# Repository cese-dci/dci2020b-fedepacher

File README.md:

Repositorio para la materia Diseño de Circuitos Impresos de la CESE2020

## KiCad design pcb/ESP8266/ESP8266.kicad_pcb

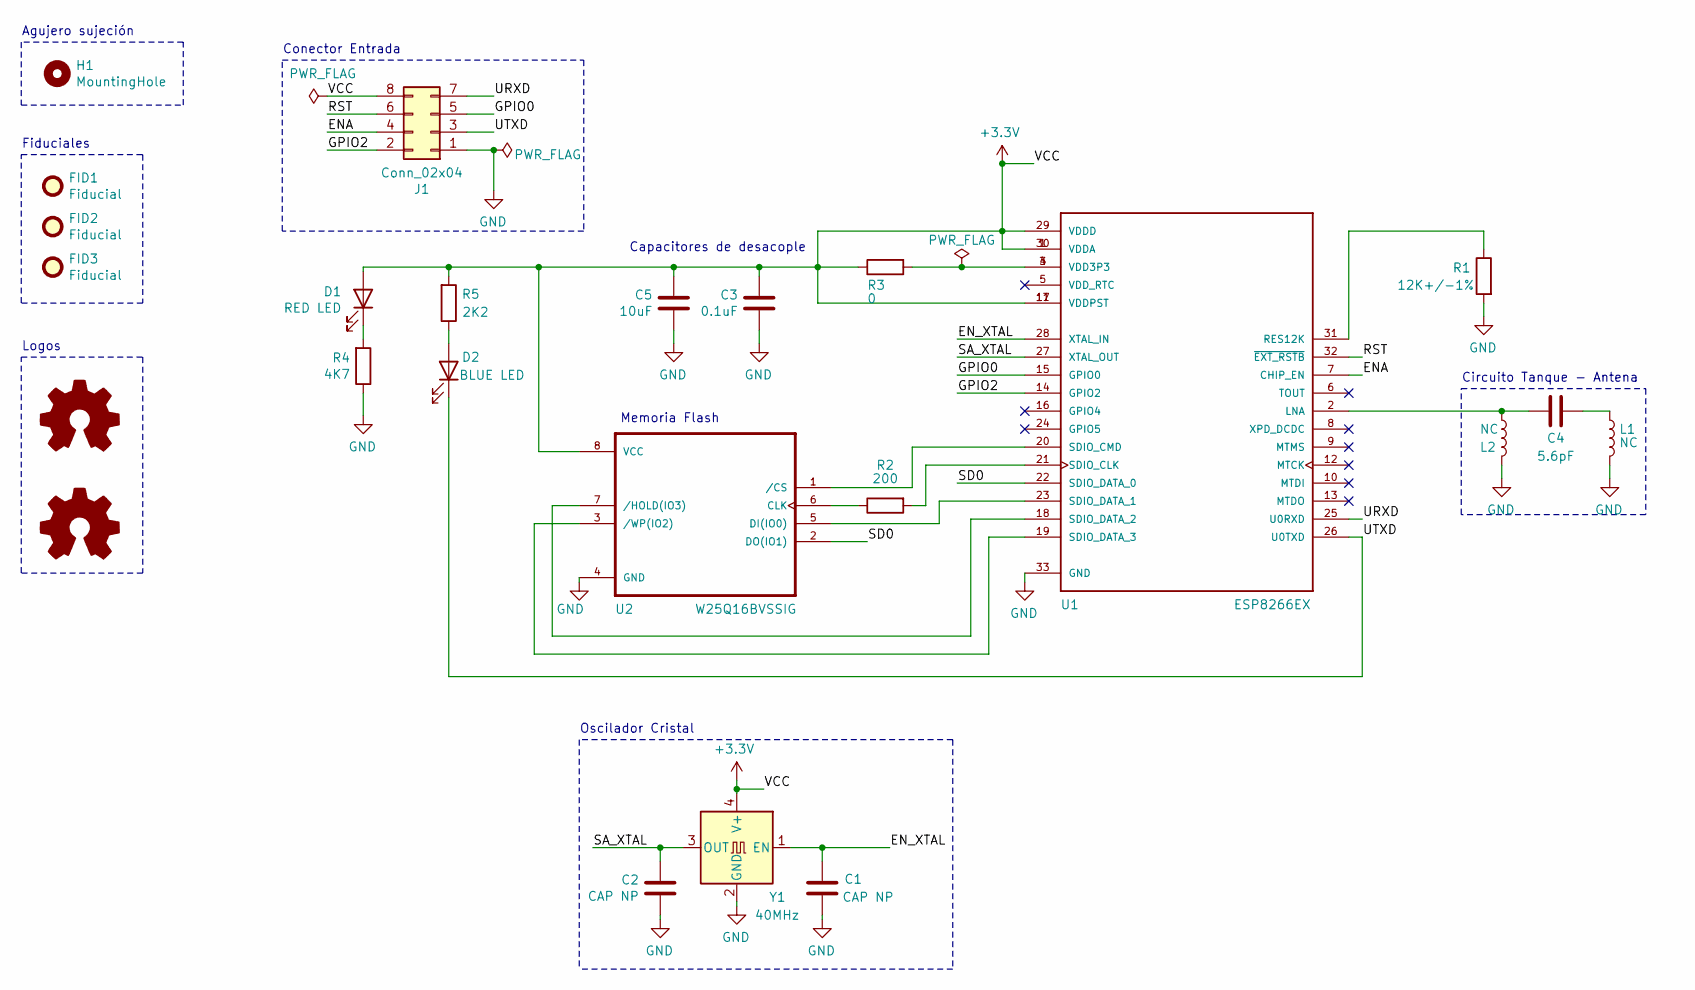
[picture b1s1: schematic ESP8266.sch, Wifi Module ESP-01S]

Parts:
C1, C2: CAP NP; C_0805_2012Metric; Digikey Nr 399-1170-2-ND
C3: 0.1uF; C_0805_2012Metric; Digikey Nr 399-1170-2-ND
C4: 5.6pF; C_0805_2012Metric; Digikey Nr 399-1170-2-ND
C5: 10uF; C_0805_2012Metric; Digikey Nr 399-1170-2-ND
D1: RED LED; R_0805_2012Metric; Digikey Nr 475-1410-2-ND
D2: BLUE LED; R_0805_2012Metric; Digikey Nr 475-1410-2-ND
FID1, FID2, FID3: Fiducial; Fiducial_1mm_Mask2mm
H1: MountingHole; MountingHole_2mm
J1: Conn_02x04; PinHeader_2x04_P2.54mm_Vertical
L1, L2: NC; L_0805_2012Metric; Digikey Nr 399-9583-2-ND
LOGO1: Logo_Open_Hardware_Small; KiCad-Logo2_5mm_Copper
LOGO2: Logo_Open_Hardware_Small; OSHW-Logo2_7.3x6mm_Copper
R1: 12K+/-1%; R_0805_2012Metric; Digikey Nr 311-390ARTR-ND
R2: 200; R_0805_2012Metric; Digikey Nr 311-390ARTR-ND
R3: 0; R_0805_2012Metric; Digikey Nr 311-390ARTR-ND
R4: 4K7; R_0805_2012Metric; Digikey Nr 311-390ARTR-ND
R5: 2K2; R_0805_2012Metric; Digikey Nr 311-390ARTR-ND
U1: ESP8266EX; QFN50P500X500X80-33N
U2: W25Q16BVSSIG; SOIC127P790X216-8N; Digikey Nr W25Q16BVSSIG-ND
Y1: 40MHz; Oscillator_SMD_EuroQuartz_XO32-4Pin_3.2x2.5mm; Digikey Nr 535-ABM8W-32.0000MHZ-4-D1X-T3TR-ND

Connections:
+3V3: C3.1, C5.1, D1.2 (A), J1.8, R3.1, R5.2, U1.1 (VDDA), U1.11 (VDDPST), U1.17 (VDDPST), U1.29 (VDDD), U1.30 (VDDA), U2.8 (VCC), Y1.4 (V+)
/ENA: J1.4, U1.7 (CHIP_EN)
/EN_XTAL: C1.1, U1.28 (XTAL_IN), Y1.1 (EN)
/GPIO0: J1.5, U1.15 (GPIO0)
/GPIO2: J1.2, U1.14 (GPIO2)
/RST: J1.6, U1.32 (~EXT_RSTB~)
/SA_XTAL: C2.1, U1.27 (XTAL_OUT), Y1.3 (OUT)
/SD0: U1.22 (SDIO_DATA_0), U2.2 (DO(IO1))
/URXD: J1.7, U1.25 (U0RXD)
/UTXD: D2.1 (K), J1.3, U1.26 (U0TXD)
GND: C1.2, C2.2, C3.2, C5.2, J1.1, L1.1, L2.1, R1.2, R4.1, U1.33 (GND), U2.4 (GND), Y1.2 (GND)
unnamed: C4.1, L2.2, U1.2 (LNA)
unnamed: C4.2, L1.2
unnamed: D1.1 (K), R4.2
unnamed: D2.2 (A), R5.1
unnamed: R1.1, U1.31 (RES12K)
unnamed: R2.1, U2.6 (CLK)
unnamed: R2.2, U1.21 (SDIO_CLK)
unnamed: R3.2, U1.3 (VDD3P3), U1.4 (VDD3P3)
unnamed: U1.18 (SDIO_DATA_2), U2.7 (/HOLD(IO3))
unnamed: U1.19 (SDIO_DATA_3), U2.3 (/WP(IO2))
unnamed: U1.20 (SDIO_CMD), U2.1 (/CS)
unnamed: U1.23 (SDIO_DATA_1), U2.5 (DI(IO0))

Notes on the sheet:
Capacitores de desacople
Memoria Flash
Circuito Tanque - Antena
Conector Entrada
Agujero sujeción
Fiduciales
Oscilador Cristal
Logos

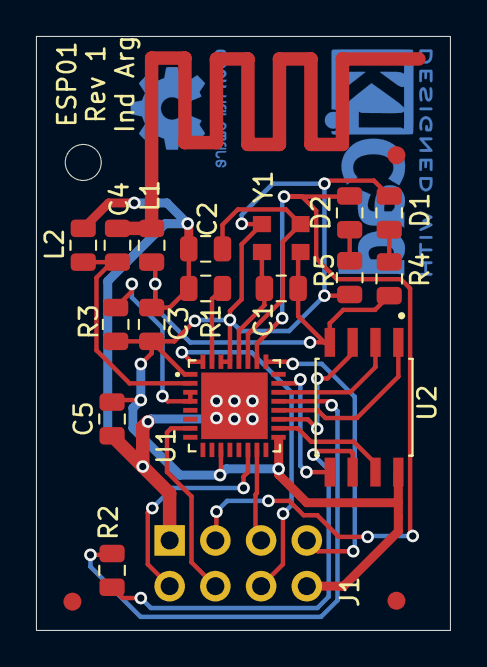
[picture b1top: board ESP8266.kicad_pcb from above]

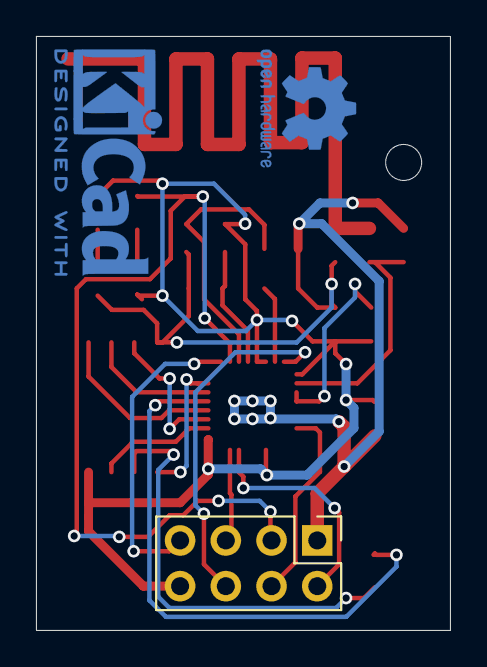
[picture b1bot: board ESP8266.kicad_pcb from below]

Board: 2 copper layers, 23.0 x 33.0 mm, 24 parts (3 on the bottom side), 23 nets.

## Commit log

2020-09-01 primer commit
2020-09-01 agregado de hojas de dato del modulo ESP01
2020-09-24 agregado de esquematico y pcb
2020-10-01 modificacion linea esquematico, avances en pcb
2020-10-02 agregado de librerias del integrado esp8266 y memoria flash w25q16bvssig
2020-10-02 agregado de referencias a datasheet en comonente
2020-10-03 cambio de footprint en las resistencias y capacitores, fin de pcb V1.0
2020-10-03 arreglo de pistas desplazadas
2020-10-03 agregado de modelos 3D al board
2020-10-09 mejoras en el pcb
2020-10-10 agregado de modelos 3D al proeycto, fiduciales y agujero
2020-10-10 correcciones
2020-10-16 reacomodamiento en esquematico
2020-10-16 board acomodado con componentes 0805
2020-10-16 agregado de comentarios
2020-10-16 agregados componentes digikey
2020-11-05 agregado de logos y e informacion para fabricacion

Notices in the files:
pcb/ESP8266/ESP8266.kicad_pcb:
CERN Open Hardware Licence Version 2 - Permissive
